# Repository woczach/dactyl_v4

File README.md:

# Dactyl v4

Custom split ergonomic keyboard project based on a Dactyl Manuform-style shell, adapted around a flexible main PCB, a custom thumb cluster, and trackball support.

This repository contains the KiCad design files, printable case parts, and reference images used during the build.

## Overview

This project is my own Dactyl-style keyboard design. The main board is a custom flexible PCB, while the extra keys and thumb-cluster approach were informed by an existing open hardware reference.

Design references used for this build:

- Dactyl Manuform base shape and layout:
[ryanis.cool keyboard link](https://ryanis.cool/cosmos/beta#cm:Ct0CCigSDhDwbSA7QABIAGIDRjEwEgUQgG8gJxICIBMSAiAAEgA4HkCAwuADCicSDRDwYSA7QABIAGICRjkSBRCAYyAnEgIgExICIAASAxCwOzgKQAAKKhINEPBVIDtAAEgAYgJGOBIFEIBXICcSAiATEgIgABIDELAvOAlAgPC8AgokEg0Q8EkgO0AASABiAkY3EgUQgEsgJxICIBMSAiAAEgA4HUAACiQSDRDwPSA7QABIAGICRjYSBRCAPyAnEgIgExICIAASADgxQAAKPRIKEHAYRSA7QABIABIJEIABICdiAkYxEgIgExIMCIA4IABIgPoaWIMGEg8IgDBArYDMA0iA6iJY6wVQuQUKQxIIEHAgO0AASAASCRCAASAnYgJGMRIKCIAwIBNAHlioBBIMCIAoEKCACiAAWI4EEgoIgEAQMEAdWNoEQIDKkRRQ9gMYAEDohaCu8FVI2pyKMArEAQolEhkIgEAQQBjADED2ibjaBkian9SG0bATUPICMIAoOMAMQJaKAQodEhMQwIACIChA7Ye0xIAISICAtL8BOKgUQICA0AEKJhIZCIAgEEAYkBwgKEDeiYy1wFNI0IukptCxBzCAKDiQHEC/qJwBChoSEBBAIChA6IektcAHSICAhFw4+CNAgIDgDAodEhMQQCAAMMgBQJTOkuApSICAsKwBMBY4AEC1mAYYCiIJCAAQyAEYACAAQLGfoI2QBEiEj5TWoHgKwAIKJxINEPABIDtAAEgAYgJGMRIFEIADICcSAiATEgIgABIAOB1AgMLgAwokEg0Q8A0gO0AASABiAkYyEgUQgA8gJxICIBMSAiAAEgA4CUAACicSDRDwGSA7QABIAGICRjMSBRCAGyAnEgIgExICIAASADgKQIDwvAIKJBINEPAlIDtAAEgAYgJGNBIFEIAnICcSAiATEgIgABIAOB5AAAokEg0Q8DEgO0AASABiAkY1EgUQgDMgJxICIBMSAiAAEgA4MkAACiYSChBwGEYgO0AASAASChCAbSAnYgNGMTASAiATEgIgABIAOEZAAApEEggQcCA7QABIABIOEIBtGDEgJ0hBYgNGMTASCAiAMCATWKUEEgwIgDgQoIAKIABYvwQSCQiAQBAwGDtARTgxQIDKkRQYAUDnhaCu8FVI2pqKKAqOAQofEgcQQCAOQMMNEhIIgDggBUDn3gZIgIC43wNYlAI4FAorEhIQwIACGABAgqIHSICAkP0DUHISEwiAOBBAGABAgFZIgICg7ANQhQE4AAohEhIQQEDzpItISICAkP0DUFpYlQESCQiAICAPQIKcCzgTGAMiCgjIARDIARgAIABAto/MpvA1SJuPuN6gmhwiBSCEByguggECBAJYR2gA)
  
- Extra keys for thumb-cluster:
  [MxLEDBitPCB](https://github.com/swanmatch/MxLEDBitPCB/blob/master/readme_en.md)

## Gallery

### 3D keyboard visualization

### Main flexible PCB

### Extra keys / thumb cluster reference

## Repository Contents

- `dactyl_v4/3dForm/printfiles/` contains the printable case, plate, and holder STL files.
- `dactyl_v4/Kicad/flex/` contains the main KiCad project for the flexible PCB design.
- `pictures/` contains reference renders and PCB images used in this README.

## Hardware Summary

- Split ergonomic Dactyl-style keyboard
- Custom flexible main PCB
- Separate thumb / extra-key area inspired by MxLEDBitPCB
- Trackball support using a PMW3360 or PMW3389 sensor
- Dual RP2040 controller setup with TRRS interconnect

## Bill of Materials

Prices below reflect the sourced parts actually purchased for this build. Items not covered by that list are left blank.

| Category | Item | Qty | Notes | Total |
| --- | --- | ---: | --- | ---: |
| Keys and switches | Womier Retro Brown Gray PBT keycap set | 1 | 138-key Cherry-profile set | 51.39 PLN |
| Keys and switches | PBTfans Doppelganger 40s kit | 1 | Child kit, 40s | 77.19 PLN |
| Keys and switches | MX-compatible switches | 90 | Outemu Silent Cream Yellow Pro, bought as one 90-pack | 71.19 PLN |
| Keys and switches | 1N4148 diodes | 100 | 1N4148W T4 SOD-123, bought as one 100-pack | 5.72 PLN |
| Pointing device and mechanical parts | 34 mm trackball | 1 | GBALL34RN, purple | 47.79 PLN |
| Pointing device and mechanical parts | PMW3360 or PMW3389 sensor | 1 | PMW3389 module | 69.19 PLN |
| Pointing device and mechanical parts | 3 x 6 x 2.5 mm bearings | 5 | Bought as one 5-pack | 9.41 PLN |
| Pointing device and mechanical parts | 3 x 8 mm dowel pins | 10 | M3, bought as one 10-pack | 4.90 PLN |
| Pointing device and mechanical parts | Tindie-supported PCB for sensor assembly | 1 | Use a compatible board as required by the sensor setup |  |
| Electrical | RP2040 Black Board USB-C | 2 | Aliexpress boards |  |
| Electrical | PJ-320A TRRS connectors | 10 | Bought as one 10-pack | 6.29 PLN |
| Electrical | TRRS cable | 1 | 3.5 mm TRRS spring coiled cable, 90-degree male-to-male | 13.99 PLN |
| Electrical | Flexible PCB fabrication | 1 | Main flex PCB, converted from 30 USD | 110.61 PLN |
| Electrical | Extra PCB fabrication | 1 | Auxiliary PCB, converted from 2 USD | 7.37 PLN |
| Electrical | Kailh hot-swap sockets | 3 | 40-piece packs, CPG1511 | 45.03 PLN |
| Electrical | SK6812MINI-E LEDs | 1 | 100-piece lot | 34.89 PLN |
| Electrical | Wire-wrap or magnet wire spool | 1 | Internal wiring |  |
| Mounting | M3 x 6 mm flat head screws | 18 | Bottom plate and microcontroller holder |  |
| Mounting | M3 x 8 mm flat head screws | 2 | Microcontroller holder through bottom plate |  |
| Mounting | M3 screw inserts | 20 | Heat-set or press-fit, depending on print and process |  |
| Other parts | 3D print service | 1 | Case and related printed parts | 100.00 PLN |

**Summary price:** 654.96 PLN

## Attribution

This repository is a custom project, but it explicitly builds on ideas and references from the following sources:

- Ryanis Cosmos for the Dactyl Manuform base geometry and layout exploration
- Swanmatch MxLEDBitPCB for ideas around extra keys and thumb-cluster implementation

The main board design in this repository is my own custom flexible PCB adaptation.

## License

This repository is distributed under the license included in [LICENSE](LICENSE).

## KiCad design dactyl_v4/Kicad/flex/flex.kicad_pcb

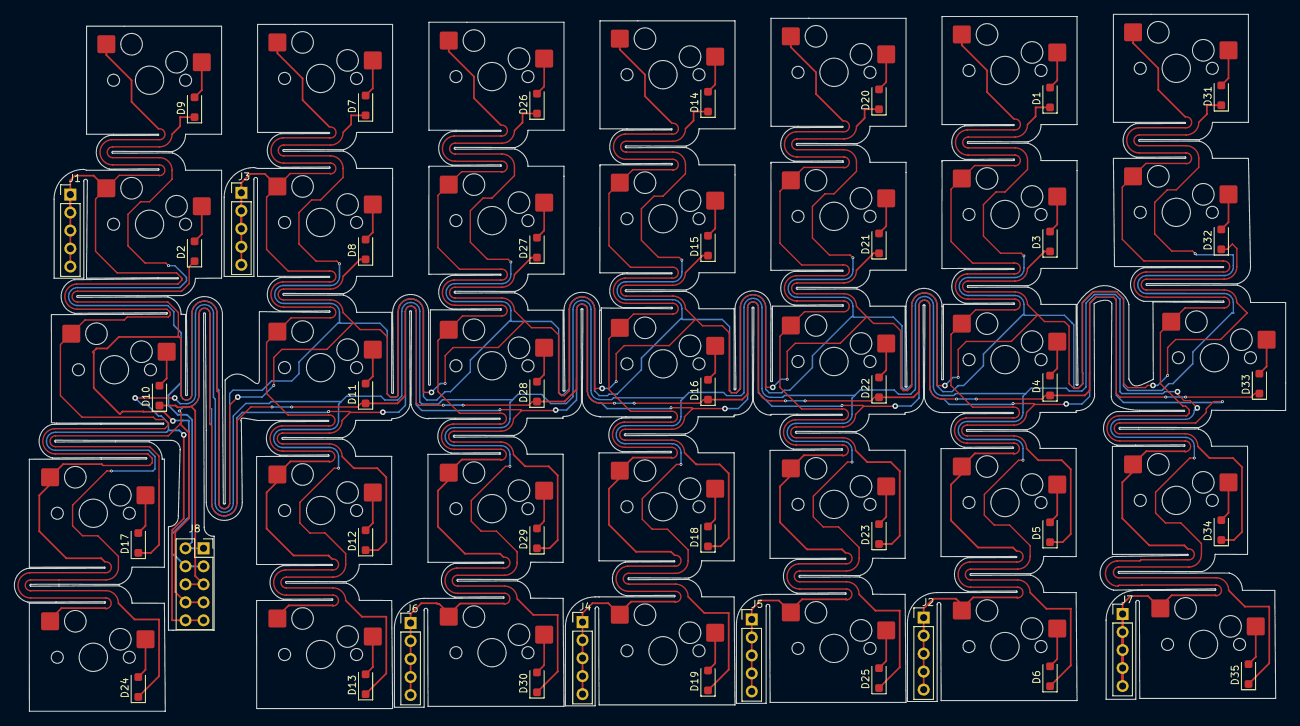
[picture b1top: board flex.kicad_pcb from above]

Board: 2 copper layers, 179.4 x 98.3 mm, 78 parts (0 on the bottom side), 47 nets.

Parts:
D1, D2, D3, D4, D5, D6, D7, D8, D9, D10, D11, D12, D13, D14, D15, D16, D17, D18, D19, D20, D21, D22, D23, D24, D25, D26, D27, D28, D29, D30, D31, D32, D33, D34, D35: D; D_SOD-123F
J1, J2, J3, J4, J5, J6, J7: Conn_01x05; PinHeader_1x05_P2.54mm_Vertical
J8: Conn_02x05_Counter_Clockwise; PinSocket_2x05_P2.54mm_Vertical
SW1, SW2, SW3, SW4, SW5, SW6, SW7, SW8, SW9, SW10, SW11, SW12, SW13, SW14, SW15, SW16, SW17, SW18, SW19, SW20, SW21, SW22, SW23, SW24, SW25, SW26, SW27, SW28, SW29, SW30, SW31, SW32, SW33, SW34, SW35: SW_Push; MX100H

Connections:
COL1: J1.1, J1.2, J1.3, J1.4, J1.5, SW2.1, SW9.1, SW10.1, SW17.1, SW24.1
COL2: J2.1, J2.2, J2.3, J2.4, J2.5, SW1.1, SW3.1, SW4.1, SW5.1, SW6.1
COL3: J3.1, J3.2, J3.3, J3.4, J3.5, SW7.1, SW8.1, SW11.1, SW12.1, SW13.1
COL4: J4.1, J4.2, J4.3, J4.4, J4.5, SW14.1, SW15.1, SW16.1, SW18.1, SW19.1
COL5: J5.1, J5.2, J5.3, J5.4, J5.5, SW20.1, SW21.1, SW22.1, SW23.1, SW25.1
COL6: J6.1, J6.2, J6.3, J6.4, J6.5, SW26.1, SW27.1, SW28.1, SW29.1, SW30.1
COL7: J7.1, J7.2, J7.3, J7.4, J7.5, SW31.1, SW32.1, SW33.1, SW34.1, SW35.1
unnamed: D1.2 (A), SW1.2
unnamed: D2.2 (A), SW2.2
unnamed: D3.2 (A), SW3.2
unnamed: D4.2 (A), SW4.2
unnamed: D5.2 (A), SW5.2
unnamed: D6.2 (A), SW6.2
unnamed: D7.2 (A), SW7.2
unnamed: D8.2 (A), SW8.2
unnamed: D9.2 (A), SW9.2
unnamed: D10.2 (A), SW10.2
unnamed: D11.2 (A), SW11.2
unnamed: D12.2 (A), SW12.2
unnamed: D13.2 (A), SW13.2
unnamed: D14.2 (A), SW14.2
unnamed: D15.2 (A), SW15.2
unnamed: D16.2 (A), SW16.2
unnamed: D17.2 (A), SW17.2
unnamed: D18.2 (A), SW18.2
unnamed: D19.2 (A), SW19.2
unnamed: D20.2 (A), SW20.2
unnamed: D21.2 (A), SW21.2
unnamed: D22.2 (A), SW22.2
unnamed: D23.2 (A), SW23.2
unnamed: D24.2 (A), SW24.2
unnamed: D25.2 (A), SW25.2
unnamed: D26.2 (A), SW26.2
unnamed: D27.2 (A), SW27.2
unnamed: D28.2 (A), SW28.2
unnamed: D29.2 (A), SW29.2
unnamed: D30.2 (A), SW30.2
unnamed: D31.2 (A), SW31.2
unnamed: D32.2 (A), SW32.2
unnamed: D33.2 (A), SW33.2
unnamed: D34.2 (A), SW34.2
unnamed: D35.2 (A), SW35.2
ROW1: D1.1 (K), D7.1 (K), D9.1 (K), D14.1 (K), D20.1 (K), D26.1 (K), D31.1 (K), J8.1, J8.2
ROW2: D2.1 (K), D3.1 (K), D8.1 (K), D15.1 (K), D21.1 (K), D27.1 (K), D32.1 (K), J8.3, J8.4
ROW3: D4.1 (K), D10.1 (K), D11.1 (K), D16.1 (K), D22.1 (K), D28.1 (K), D33.1 (K), J8.5, J8.6
ROW4: D5.1 (K), D12.1 (K), D17.1 (K), D18.1 (K), D23.1 (K), D29.1 (K), D34.1 (K), J8.7, J8.8
ROW5: D6.1 (K), D13.1 (K), D19.1 (K), D24.1 (K), D25.1 (K), D30.1 (K), D35.1 (K), J8.9, J8.10

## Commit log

2026-03-18 next commit
2026-03-18 next commit1
